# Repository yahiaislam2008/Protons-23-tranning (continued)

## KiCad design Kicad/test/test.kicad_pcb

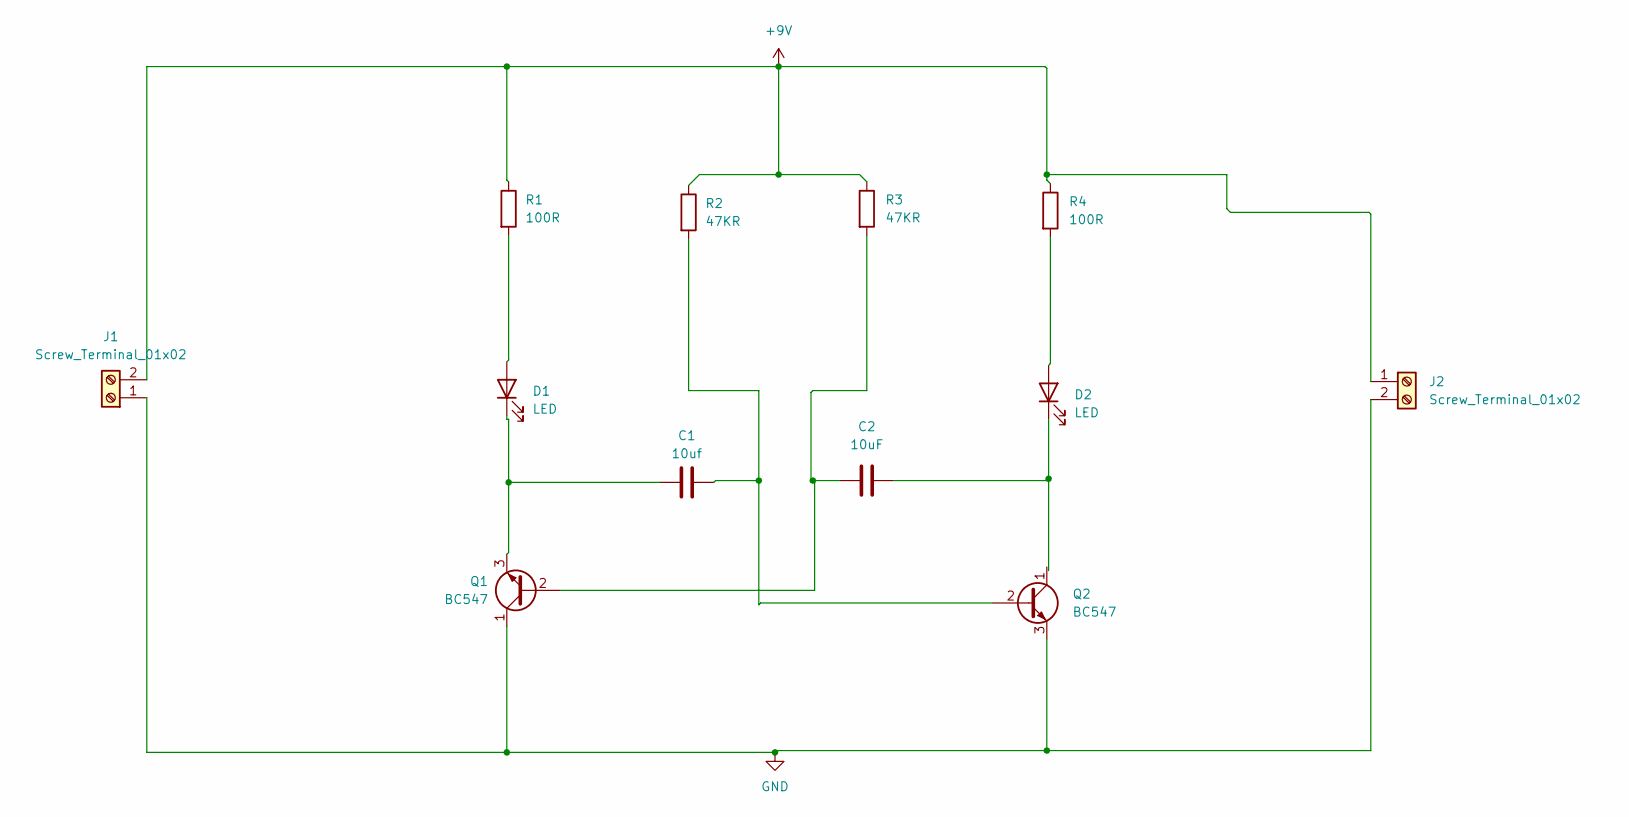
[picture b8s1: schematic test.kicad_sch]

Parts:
C1: 10uf; C_0603_1608Metric
C2: 10uF; C_0603_1608Metric
D1, D2: LED; LED_0201_0603Metric
J1, J2: Screw_Terminal_01x02; TerminalBlock_Phoenix_MKDS-1,5-2-5.08_1x02_P5.08mm_Horizont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
Q1, Q2: BC547; TO-92_Inline
R1, R4: 100R; R_0201_0603Metric
R2, R3: 47KR; R_0201_0603Metric

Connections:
+9V: J1.2, J2.1, R1.1, R2.1, R3.1, R4.1
GND: J1.1, J2.2, Q1.1 (C), Q2.3 (E)
unnamed: D1.2 (A), R1.2
unnamed: C1.1, D1.1 (K), Q1.3 (E)
unnamed: D2.2 (A), R4.2
unnamed: C2.2, D2.1 (K)
unnamed: C2.1, Q1.2 (B), R3.2
unnamed: C1.2, Q2.2 (B), R2.2

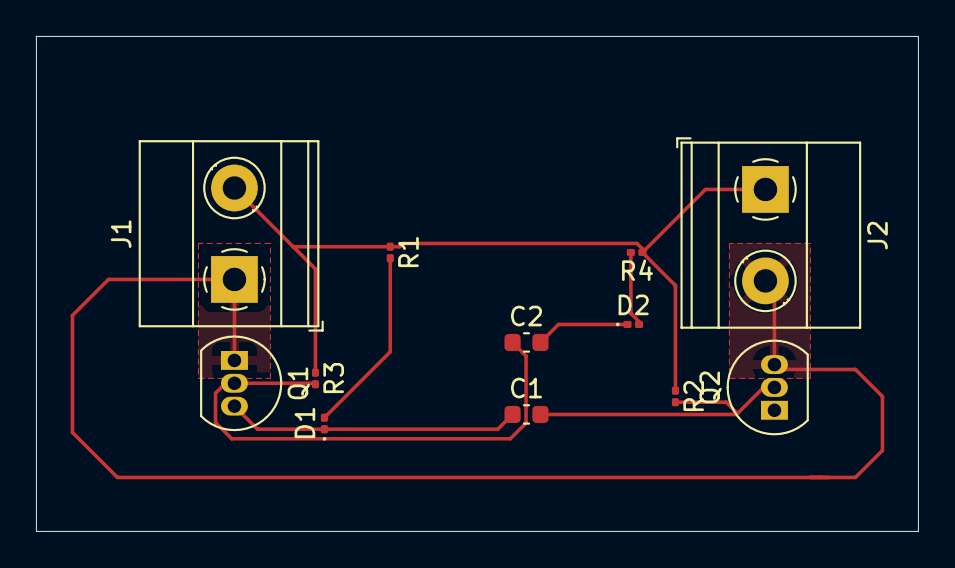
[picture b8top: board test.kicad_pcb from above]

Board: 2 copper layers, 49.0 x 27.5 mm, 12 parts (0 on the bottom side), 8 nets.

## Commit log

2024-05-13 Protons'23 files
2024-05-13 trannings
2024-12-13 robotics
2024-12-14 Robotics_2
2024-12-14 games
